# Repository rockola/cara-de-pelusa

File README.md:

# cara-de-pelusa

NPN Fuzz Face

* v0.1: initial import, unverified

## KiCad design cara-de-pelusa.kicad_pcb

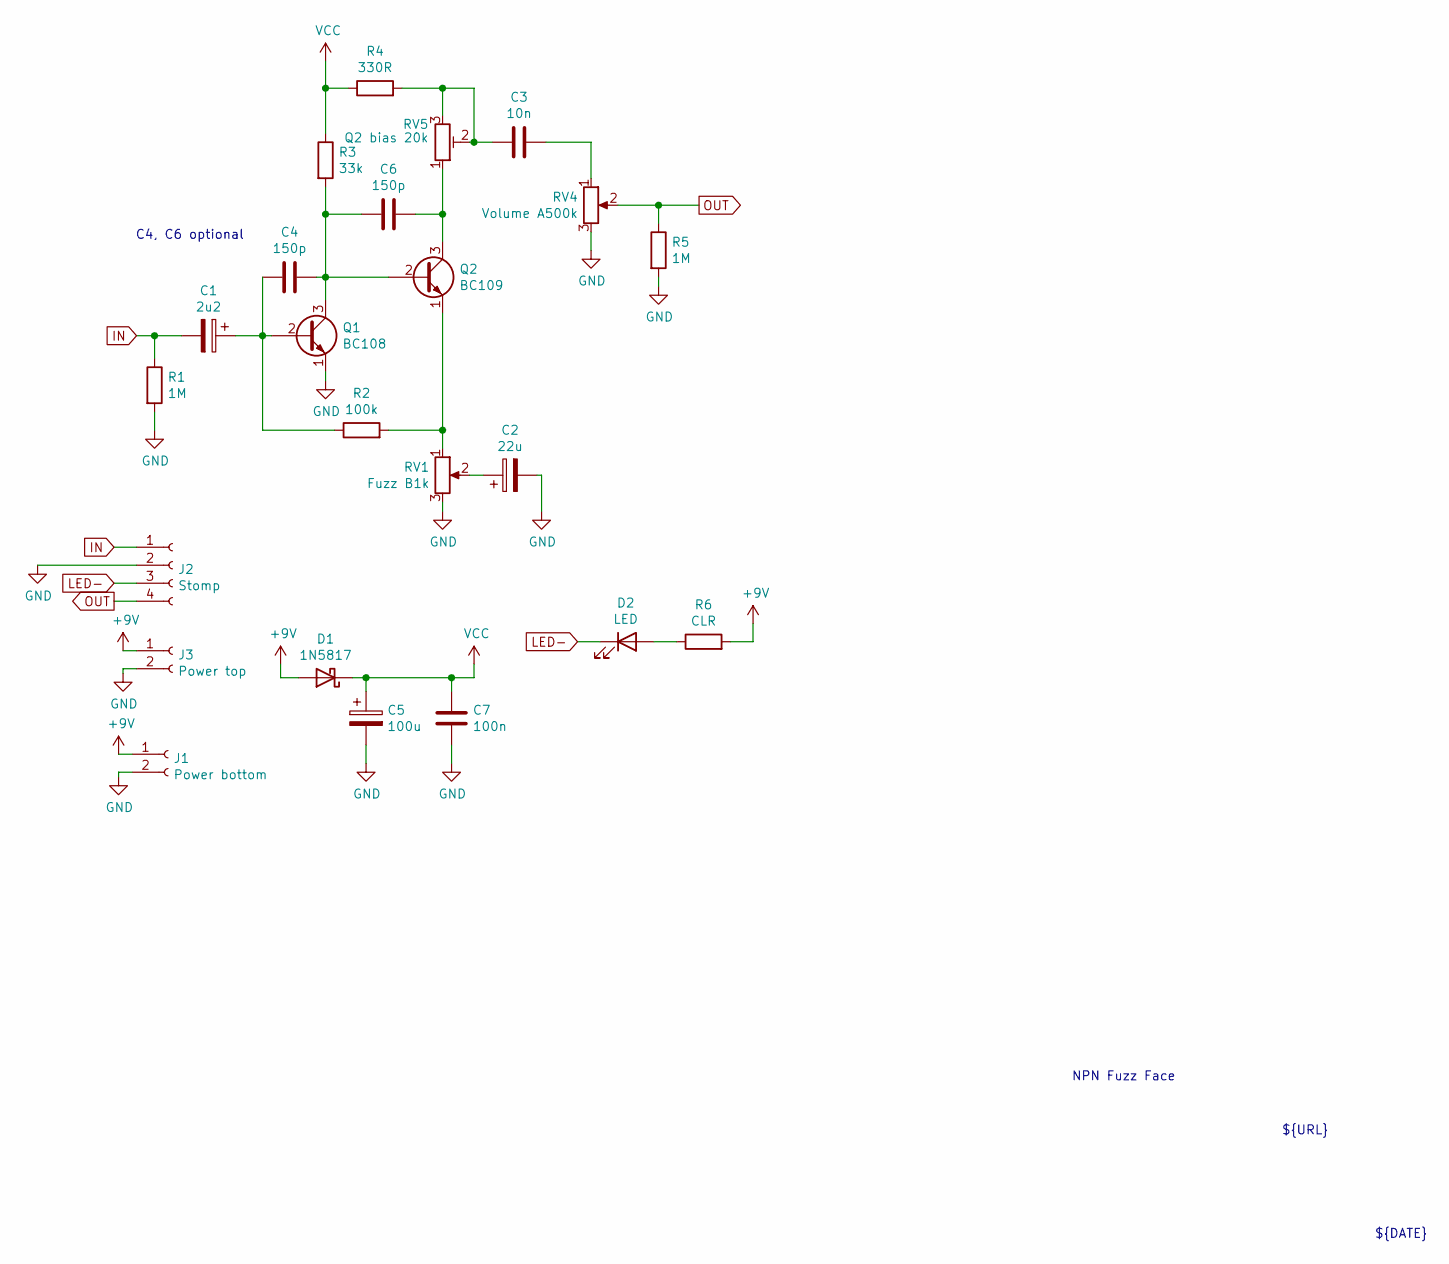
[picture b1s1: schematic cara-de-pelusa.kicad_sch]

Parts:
C1: 2u2; CP_D5.0_P2.50
C2: 22u; CP_D5.0_P2.50
C3: 10n; C_Box_7.2_2.5
C4, C6: 150p; C_Box_7.2_2.5
C5: 100u; CP_D5.0_P2.50
C7: 100n; C_Box_7.2_2.5
D1: 1N5817; D_DO-41_SOD81_P10.16mm_Horizontal
D2: LED; LED.3mm
J1: Power bottom; Power_Header_2pin
J2: Stomp; Stomp_4pin
J3: Power top; Power_Header_2pin_TOP
Q1: BC108; TO92_EBCE
Q2: BC109; TO92_EBCE
R1, R5: 1M; R_DIN0207
R2: 100k; R_DIN0207
R3: 33k; R_DIN0207
R4: 330R; R_DIN0207
R6: CLR; R_DIN0207
RV1: Fuzz B1k; 9mm metal shaft
RV4: Volume A500k; 9mm metal shaft
RV5: Q2 bias 20k; TRIM1

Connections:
+9V: D1.2 (A), J1.1, J3.1, R6.2
GND: C2.2, C5.2, C7.2, J1.2, J2.2, J3.2, Q1.1 (E), R1.2, R5.2, RV1.3, RV4.3
IN: C1.2, J2.1, R1.1
LED-: D2.1 (K), J2.3
unnamed: C1.1, C4.1, Q1.2 (B), R2.1
unnamed: C2.1, RV1.2
unnamed: C3.1, R4.2, RV5.2, RV5.3
unnamed: C3.2, RV4.1
unnamed: C4.2, C6.1, Q1.3 (C), Q2.2 (B), R3.2
unnamed: C6.2, Q2.3 (C), RV5.1
unnamed: D2.2 (A), R6.1
unnamed: Q2.1 (E), R2.2, RV1.1
OUT: J2.4, R5.1, RV4.2
VCC: C5.1, C7.1, D1.1 (K), R3.1, R4.1

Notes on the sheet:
${DATE}
NPN Fuzz Face
C4, C6 optional
${REVISION}
${URL}
${TITLE}

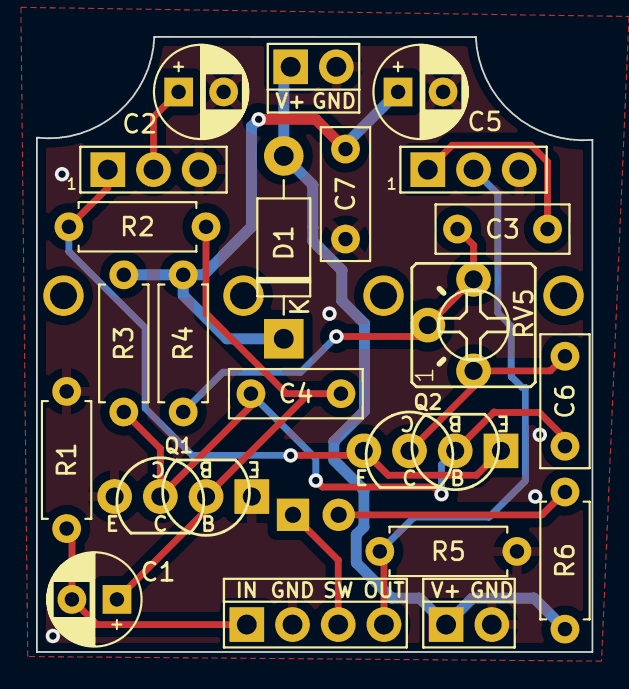
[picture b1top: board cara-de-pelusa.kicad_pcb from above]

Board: 2 copper layers, 30.9 x 34.2 mm, 23 parts (1 on the bottom side), 14 nets.

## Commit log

2020-08-26 initial
2020-08-26 9mm onboard pots
2020-08-26 v0.1: submitted to Oshpark for verification
2020-08-26 preview images from Oshpark, schematic screenshot
2022-01-11 updated to KiCad 6.0
